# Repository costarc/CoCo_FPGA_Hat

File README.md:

# CoCo_FPGA_Hat
A Cartridge interface that converts TRS-Color 5v signal levels in the bus to 3.3v, exposed over an IDC connector for external devices that operates at 3.3v level.

Even though this project was developed and tested with FPGA development boards Terasic DE0 and DE1, the interface can actually interface with any 3.3v device, even microcontrollers, to implement peripherals for the TRS-80 Color computer.

This project as adapted from my MSX DE1 hat for DE1 (https://github.com/costarc/MSX_FPGA_Hat).

Project Status: RIP. Project was assembled and tested, proven to work. Sample test project is available in the folder Reference Designs, which demonstrate how to implement a Cartridge ROM using the interface and a connected Terasic DE0.

Because it was not extensively tested and no other designs developed, there might be limitations on which functions it might be able to implement, therefore build at your own risk! :)

# Technical Description of the Interface
The interface connects the computer BUS to the FPGA GPIOs, using the flat cable.
The interface should be connected to JP2 of DE1, which corresponds to GPIO_1. This is the GPIO used in all the reference designs in this project. To use JP1 (GPIO_0), all pins must be remapped for the projects.

Address and control signals always flow from the computer to the FPGA - the DIR and /OE signals in U2,U3,U4 and U5 are always asserted (pull-up for bus directoin (Pin 1) and grounded for /OE (pin 19).

For U1, the BUS direction is controlled by the computer read signal (RD_n) in MSX. When read operation is triggered (RD_n = 0), the directon of the data in U1 flows from the FPGA to the computer. At all other times, the data flows from the computer to the FPGA.

U1 has a pull-up in the /OE pin, to keep any output disabled until the FPGA drives this pin low, which should only occur when the FPGA is in fact requested by the computer. Keeping /OE high isolates the computer BUS from anythign happening in the FPGA, which is also important during the boot in the computer.

# Controlling Flow of Data in the Interface
The recommended method to drive the interace signals is as follows:

U1 bus direction (pin 1): no additional implementaton is required - this pin is controlled automatically by the computer according his operations. For example, when the CoCo computer is requesting data from the FPGA, this pin is asserted HIGH by *R/W = 1, when sending data it is asserted LOW because *R/W = 0.
Note that the FPGA pins are connected on the bus A of U1, and CoCo bus is connected in the bus B of U1 - this allowed both keep the CIs all aligned in the same direction and use the CoCo *R/W signal to drive the directon of this bus).

U1 /OE (Output Enable, pin 19): This pin should be put in LOW whenever the FPGA detects that it is being requested - for example, if a ROM is implemented in the FPGA, the address and slot decoding should detect and assert according the GPIO pin /C_U1_D_OE (name was meant to stand for "CI U1, computer Data bus, pin OE).

U2,U3,U4,U5 bus direction: also no need to be concerned - these CIs have fixed bus direction, and constantly asserted HIGH for data to flow from the 74lvc245 bus A to bus B. 
The interface has some pins being used to carry data from the FPG to the computer in these CIs, in which case the routing for such signals was made bringing in input from the GPIO to the bus A, and teh exit in the bus B reouted to the computer.

# Jumpers and Configurations

The limited number of GPIOs in the development board require that we do some compromises in the design.
Some of the less used signals were routed to jumpers, at which point they can be selected to be sent to the FPGA.

J1 allow to select one of *SLENB OR *NMI to B be connected to FPGA connector pin 39 (/C_NMI_SLENB).

# SRAM Addon
Because some development boards (such as Terasic DE0) does not have a SRAM module, it makes it difficult to implement RAM cores due to DDRAM complexity.
For this reason, I designed also a SRAM addon to plug to the DE0  GPIO. This design in in the folder "DE0_Addon_Board".

# Other Important Considerations

The interface was designed to be compatible with Terasic DEn series of boards. However, these boards present some differences in the GPIOs funtionalities, where some bords (like DE1) have 36 generic I/O pins avaialable fo rinput/output functions, and others like DE0 have four pins dedicated to either input or outputs. This is the case of pins 1 and 3, whch are input only pins, and 19, 21 which are output only.
These differences were already considered in the reference designs, and these pins assigned to functions that will not case problems of limitations to the designs.
If you want to change the pin mapping in the FPGA designs, pay attention to these pins - do not assign functions opposite to the directon they actually work.

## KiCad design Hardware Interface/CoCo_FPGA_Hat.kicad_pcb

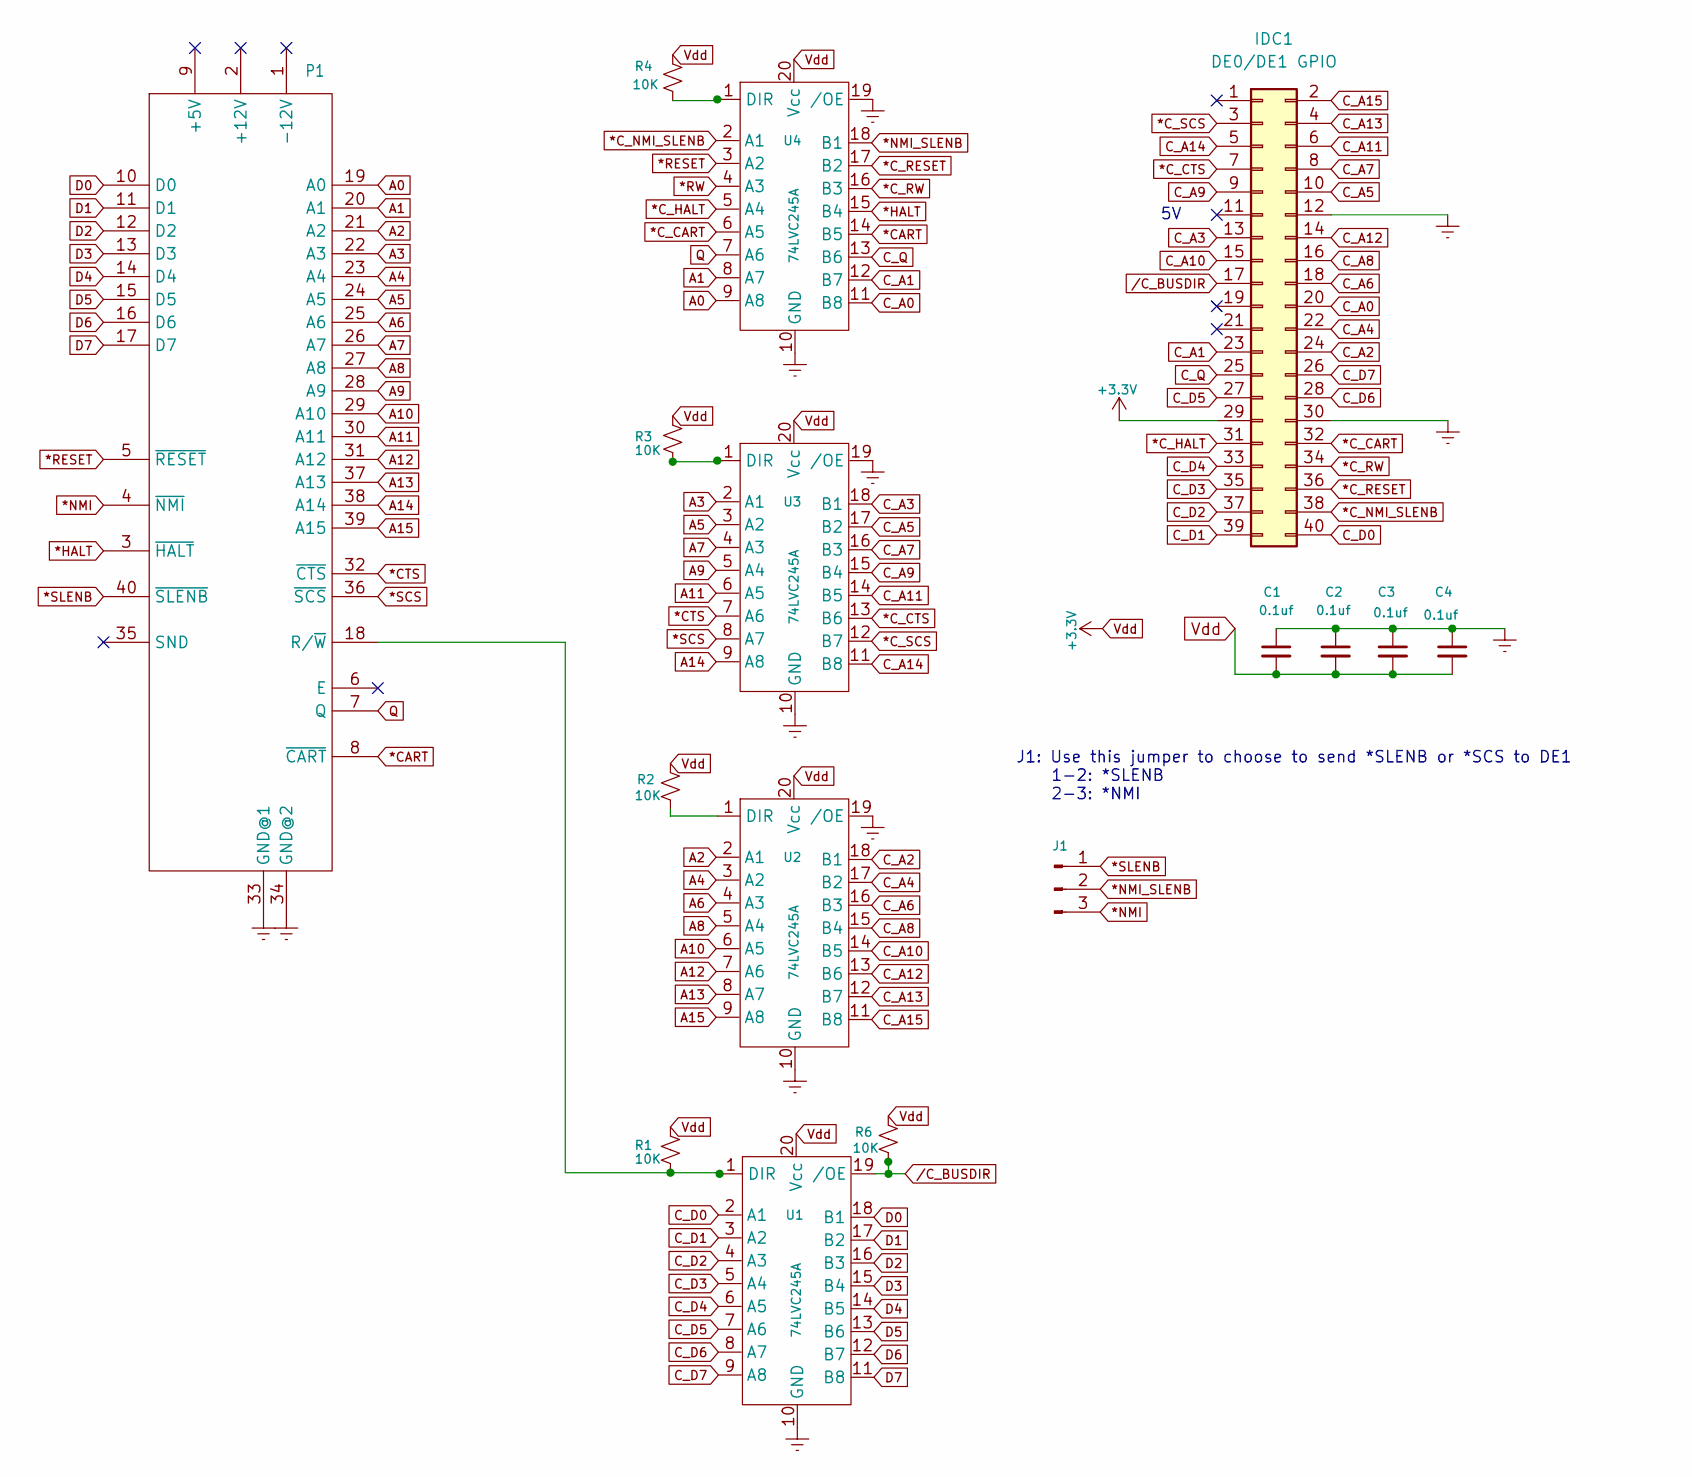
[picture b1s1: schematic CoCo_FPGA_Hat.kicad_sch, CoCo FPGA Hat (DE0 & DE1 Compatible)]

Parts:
C1, C2, C3, C4: 0.1uf; C_Disc_D3.0mm_W1.6mm_P2.50mm
IDC1: DE0/DE1 GPIO; PinHeader_2x20_P2.54mm_Vertical
J1: J1; PinHeader_1x03_P2.54mm_Vertical
P1: CoCo_Slot; COCO-CART-2.1X1.75
R1, R2, R3, R4, R6: 10K; R_Axial_DIN0204_L3.6mm_D1.6mm_P5.08mm_Horizontal
U1, U2, U3, U4: 74LVC245A; DIP-20_W7.62mm

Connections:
*CART: P1.8 (~CART), U4.14 (B5)
*CTS: P1.32 (~CTS), U3.7 (A6)
*C_CART: IDC1.32, U4.6 (A5)
*C_CTS: IDC1.7, U3.13 (B6)
*C_HALT: IDC1.31, U4.5 (A4)
*C_NMI_SLENB: IDC1.38, U4.2 (A1)
*C_RESET: IDC1.36, U4.17 (B2)
*C_RW: IDC1.34, U4.16 (B3)
*C_SCS: IDC1.3, U3.12 (B7)
*HALT: P1.3 (~HALT), U4.15 (B4)
*NMI: J1.3, P1.4 (~NMI)
*NMI_SLENB: J1.2, U4.18 (B1)
*RESET: P1.5 (~RESET), U4.3 (A2)
*RW: U4.4 (A3)
*SCS: P1.36 (~SCS), U3.8 (A7)
*SLENB: J1.1, P1.40 (~SLENB)
+5V: P1.9 (+5V)
A0: P1.19 (A0), U4.9 (A8)
A1: P1.20 (A1), U4.8 (A7)
A2: P1.21 (A2), U2.2 (A1)
A3: P1.22 (A3), U3.2 (A1)
A4: P1.23 (A4), U2.3 (A2)
A5: P1.24 (A5), U3.3 (A2)
A6: P1.25 (A6), U2.4 (A3)
A7: P1.26 (A7), U3.4 (A3)
A8: P1.27 (A8), U2.5 (A4)
A9: P1.28 (A9), U3.5 (A4)
A10: P1.29 (A10), U2.6 (A5)
A11: P1.30 (A11), U3.6 (A5)
A12: P1.31 (A12), U2.7 (A6)
A13: P1.37 (A13), U2.8 (A7)
A14: P1.38 (A14), U3.9 (A8)
A15: P1.39 (A15), U2.9 (A8)
C_A0: IDC1.20, U4.11 (B8)
C_A1: IDC1.23, U4.12 (B7)
C_A2: IDC1.24, U2.18 (B1)
C_A3: IDC1.13, U3.18 (B1)
C_A4: IDC1.22, U2.17 (B2)
C_A5: IDC1.10, U3.17 (B2)
C_A6: IDC1.18, U2.16 (B3)
C_A7: IDC1.8, U3.16 (B3)
C_A8: IDC1.16, U2.15 (B4)
C_A9: IDC1.9, U3.15 (B4)
C_A10: IDC1.15, U2.14 (B5)
C_A11: IDC1.6, U3.14 (B5)
C_A12: IDC1.14, U2.13 (B6)
C_A13: IDC1.4, U2.12 (B7)
C_A14: IDC1.5, U3.11 (B8)
C_A15: IDC1.2, U2.11 (B8)
C_D0: IDC1.40, U1.2 (A1)
C_D1: IDC1.39, U1.3 (A2)
C_D2: IDC1.37, U1.4 (A3)
C_D3: IDC1.35, U1.5 (A4)
C_D4: IDC1.33, U1.6 (A5)
C_D5: IDC1.27, U1.7 (A6)
C_D6: IDC1.28, U1.8 (A7)
C_D7: IDC1.26, U1.9 (A8)
C_Q: IDC1.25, U4.13 (B6)
D0: P1.10 (D0), U1.18 (B1)
D1: P1.11 (D1), U1.17 (B2)
D2: P1.12 (D2), U1.16 (B3)
D3: P1.13 (D3), U1.15 (B4)
D4: P1.14 (D4), U1.14 (B5)
D5: P1.15 (D5), U1.13 (B6)
D6: P1.16 (D6), U1.12 (B7)
D7: P1.17 (D7), U1.11 (B8)
GNDREF: C1.1, C2.1, C3.1, C4.1, IDC1.12, IDC1.30, P1.33 (GND@1), P1.34 (GND@2), U1.10 (GND), U2.10 (GND), U2.19 (/OE), U3.10 (GND), U3.19 (/OE), U4.10 (GND), U4.19 (/OE)
unnamed: P1.18 (R/~W), R1.2, U1.1 (DIR)
unnamed: R2.2, U2.1 (DIR)
unnamed: R3.2, U3.1 (DIR)
unnamed: R4.2, U4.1 (DIR)
Q: P1.7 (Q), U4.7 (A6)
Vdd: C1.2, C2.2, C3.2, C4.2, IDC1.29, R1.1, R2.1, R3.1, R4.1, R6.1, U1.20 (Vcc), U2.20 (Vcc), U3.20 (Vcc), U4.20 (Vcc)
/C_BUSDIR: IDC1.17, R6.2, U1.19 (/OE)

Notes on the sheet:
J1: Use this jumper to choose to send *SLENB or *SCS to DE1 1-2: *SLENB 2-3: *NMI

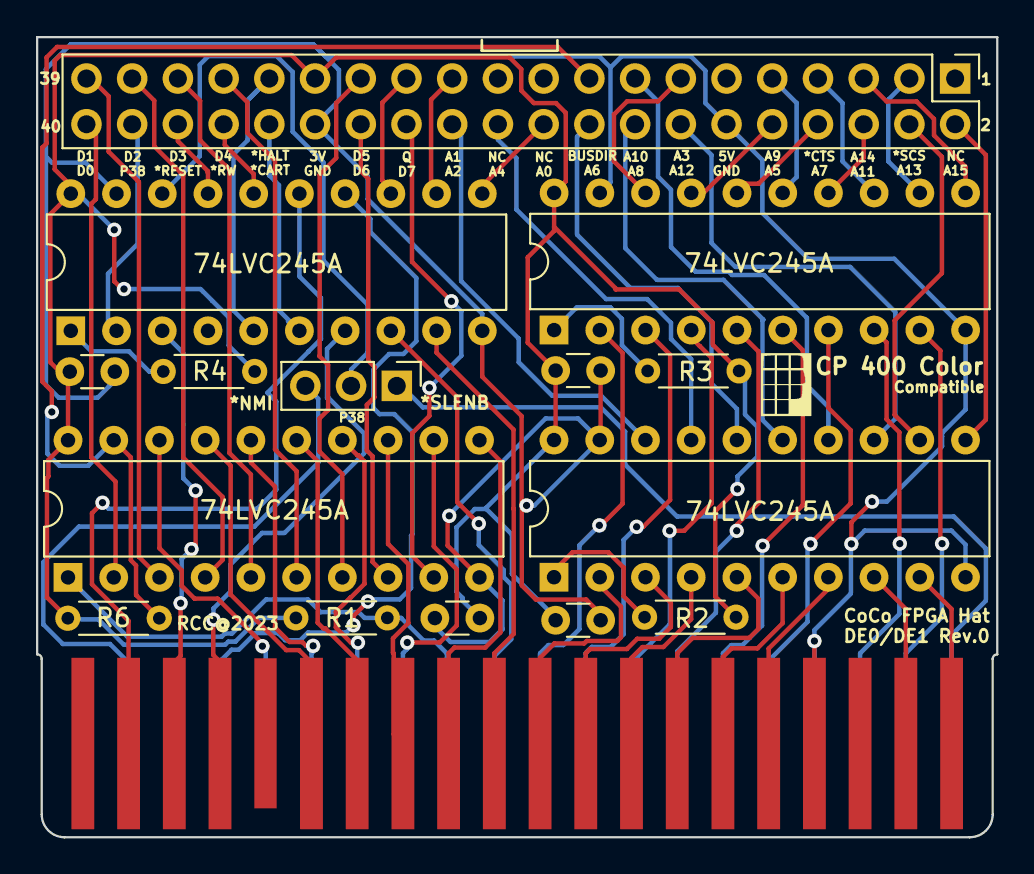
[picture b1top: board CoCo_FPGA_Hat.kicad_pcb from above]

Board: 2 copper layers, 53.3 x 44.5 mm, 16 parts (0 on the bottom side), 72 nets.

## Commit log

2023-01-15 First commit - cloned MSX project as is
2023-01-15 Adding PCB layout
2023-01-15 Project completd
2023-01-15 Small change to silk
2023-01-16 REvised PCB for CoCo, added DE0 version
2023-01-17 Added gerber files
2023-01-17 Deleted DE1 design files -> DE0 is compatible with DE1 as well
2023-01-18 Some updates to revision number and silkscreen
2023-01-21 Changed directory structure
2023-01-24 Updated pictures of pcb
2023-01-26 Re-printed the gerbers
2023-01-26 Added zip file for re-printed gerbers
2023-01-29 Added project for Add-On board SRAM 512KB for DE0
2023-01-29 Added 2nd IDC connector in paralell with the SRAM
2023-01-31 Disclaimer and removed gerber files
2023-01-31 Added proper readme
2023-01-31 Renamed signal name for U1 /OE
2023-02-16 Changed footprint of SRAM decoupling capacitors to SMD 0603; Updated SRAM Addon for Rev.2
2023-02-17 added readme
2023-03-13 Simple 8KB ROM working with the CoCo
2023-03-13 Copied instructions from Luciano Scharf
2025-06-01 latest small updated
2025-06-01 cleaned up
